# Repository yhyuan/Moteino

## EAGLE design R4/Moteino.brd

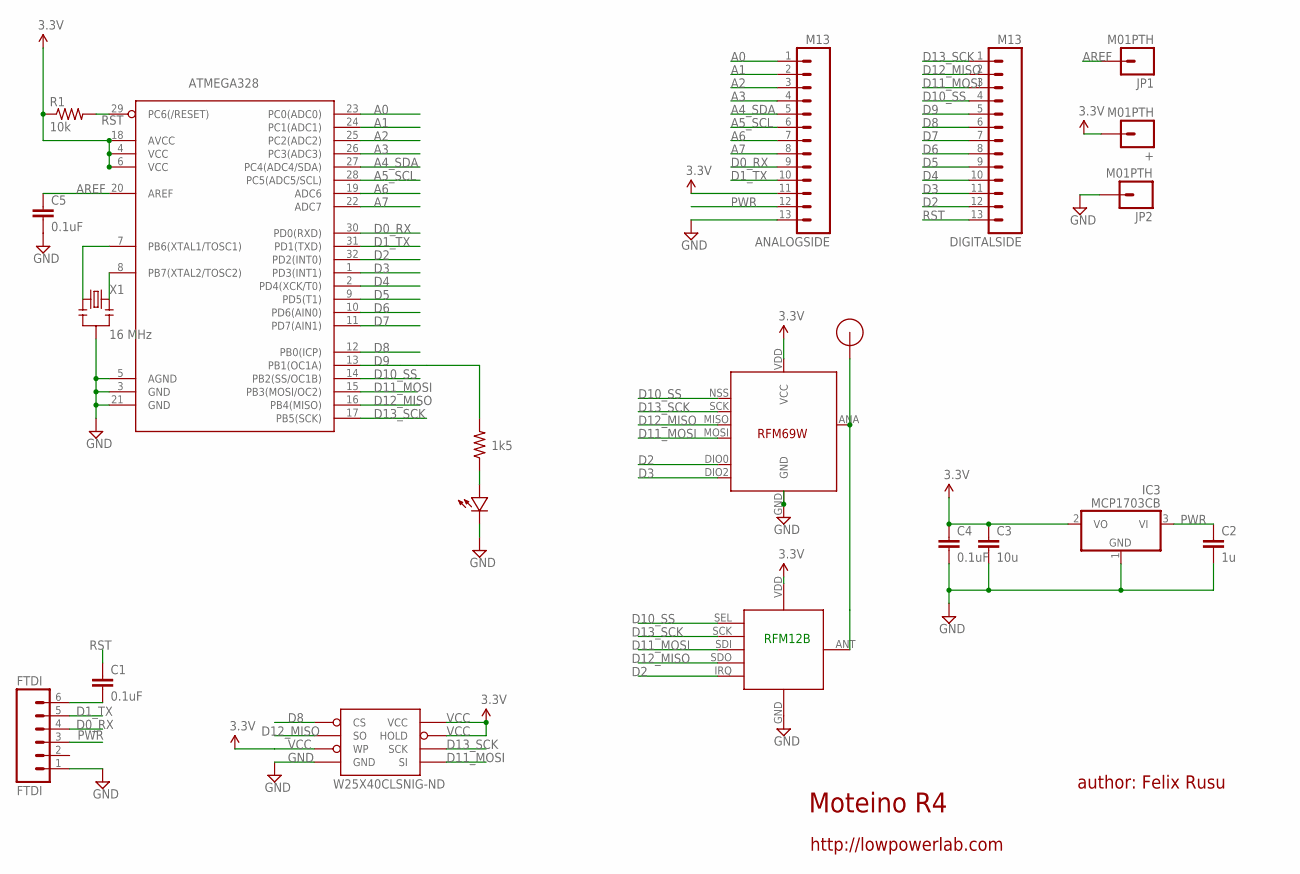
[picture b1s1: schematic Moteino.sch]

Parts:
+: M01PTH; 1X01
ANALOGSIDE: M13; 1X13
ATMEGA328: ATMega-328; TQFP32-08
C1, C4, C5: 0.1uF; 0603-CAP
C2: 1u; 0603-CAP
C3: 10u; 0805-CAP
DIGITALSIDE: M13; 1X13
FTDI: FTDI; 1X06
IC3: MCP1703CB; SOT23
JP1, JP2: M01PTH; 1X01
R1: 10k; 0603-RES
R2: 1k5; 0603-RES
RFM12B: RFM12B_MINPADS; RFM12B-MINPADS
U$1: RFM12B_ANTENNA; RFM12B-ANTENNA
U$2: LED0603; 0603-LED
U$5: RFM69; RFM69W-MINPADS
W25X40CLSNIG-ND: AT25F512BWIDE_5.3MM; SO08WIDE
X1: 16 MHz; RESONATOR-SMD

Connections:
A0: ANALOGSIDE.1, ATMEGA328.23 (PC0(ADC0))
A1: ANALOGSIDE.2, ATMEGA328.24 (PC1(ADC1))
A2: ANALOGSIDE.3, ATMEGA328.25 (PC2(ADC2))
A3: ANALOGSIDE.4, ATMEGA328.26 (PC3(ADC3))
A4_SDA: ANALOGSIDE.5, ATMEGA328.27 (PC4(ADC4/SDA))
A5_SCL: ANALOGSIDE.6, ATMEGA328.28 (PC5(ADC5/SCL))
A6: ANALOGSIDE.7, ATMEGA328.19 (ADC6)
A7: ANALOGSIDE.8, ATMEGA328.22 (ADC7)
AREF: ATMEGA328.20 (AREF), C5.1, JP1.1
D0_RX: ANALOGSIDE.9, ATMEGA328.30 (PD0(RXD)), FTDI.4
D1_TX: ANALOGSIDE.10, ATMEGA328.31 (PD1(TXD)), FTDI.5
D2: ATMEGA328.32 (PD2(INT0)), DIGITALSIDE.12, RFM12B.IRQ, U$5.DIO0
D3: ATMEGA328.1 (PD3(INT1)), DIGITALSIDE.11, U$5.DIO2
D4: ATMEGA328.2 (PD4(XCK/T0)), DIGITALSIDE.10
D5: ATMEGA328.9 (PD5(T1)), DIGITALSIDE.9
D6: ATMEGA328.10 (PD6(AIN0)), DIGITALSIDE.8
D7: ATMEGA328.11 (PD7(AIN1)), DIGITALSIDE.7
D8: ATMEGA328.12 (PB0(ICP)), DIGITALSIDE.6, W25X40CLSNIG-ND.1 (CS)
D9: ATMEGA328.13 (PB1(OC1A)), DIGITALSIDE.5, R2.2
D10_SS: ATMEGA328.14 (PB2(SS/OC1B)), DIGITALSIDE.4, RFM12B.SEL, U$5.NSS (SEL)
D11_MOSI: ATMEGA328.15 (PB3(MOSI/OC2)), DIGITALSIDE.3, RFM12B.SDI (SDI/MOSI), U$5.MOSI, W25X40CLSNIG-ND.5 (SI)
D12_MISO: ATMEGA328.16 (PB4(MISO)), DIGITALSIDE.2, RFM12B.SDO (SDO/MISO), U$5.MISO, W25X40CLSNIG-ND.2 (SO)
D13_SCK: ATMEGA328.17 (PB5(SCK)), DIGITALSIDE.1, RFM12B.SCK, U$5.SCK, W25X40CLSNIG-ND.6 (SCK)
GND: ANALOGSIDE.13, ATMEGA328.3 (GND), ATMEGA328.5 (AGND), ATMEGA328.21 (GND), C2.2, C3.2, C4.2, C5.2, FTDI.1, IC3.1 (GND), JP2.1, RFM12B.GND, U$2.MINUS, U$5.GND, W25X40CLSNIG-ND.4 (GND), X1.2
unnamed: ATMEGA328.7 (PB6(XTAL1/TOSC1)), X1.1
unnamed: R2.1, U$2.PLUS
unnamed: RFM12B.ANT, U$1.P$1, U$5.ANA (ANT)
unnamed: C1.2, FTDI.6
unnamed: ATMEGA328.8 (PB7(XTAL2/TOSC2)), X1.3
PWR: ANALOGSIDE.12, C2.1, FTDI.3, IC3.3 (VI)
RST: ATMEGA328.29 (PC6(/RESET)), C1.1, DIGITALSIDE.13, R1.2
VCC: +.1, ANALOGSIDE.11, ATMEGA328.4 (VCC), ATMEGA328.6 (VCC), ATMEGA328.18 (AVCC), C3.1, C4.1, IC3.2 (VO), R1.1, RFM12B.VDD, U$5.VDD (VCC), W25X40CLSNIG-ND.3 (WP), W25X40CLSNIG-ND.7 (HOLD), W25X40CLSNIG-ND.8 (VCC)

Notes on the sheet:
Moteino R4
author: Felix Rusu
http://lowpowerlab.com
RFM12B

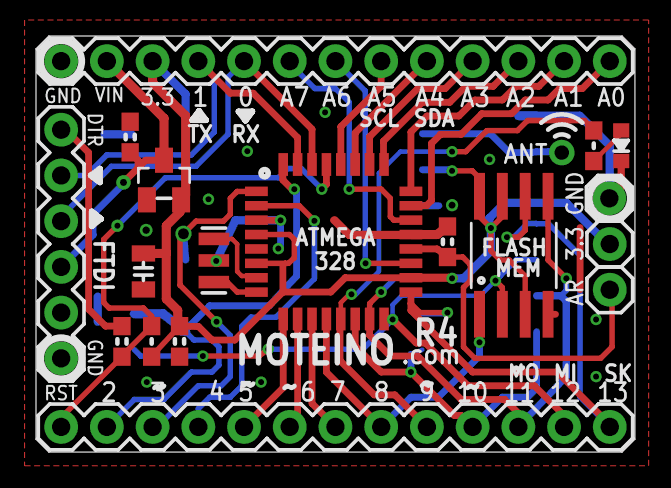
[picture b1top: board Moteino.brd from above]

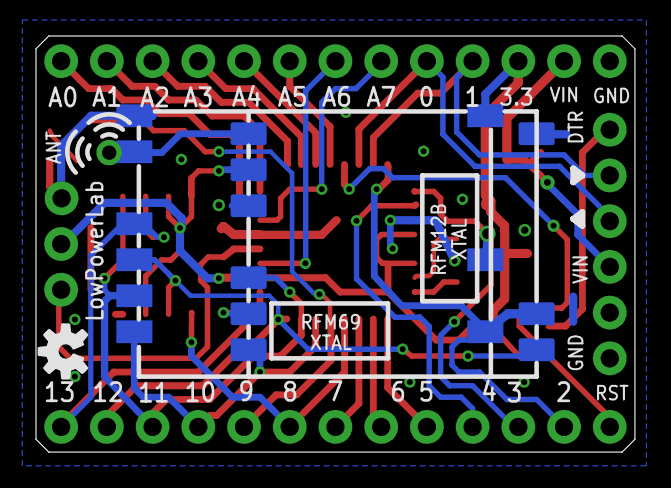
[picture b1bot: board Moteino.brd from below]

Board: 2 copper layers, 33.3 x 23.1 mm, 22 parts (3 on the bottom side), 32 nets.

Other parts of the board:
U$3: OSHW-LOGO-S

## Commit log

2015-11-10 Connect pin 3 with DIO2 https://github.com/kobuki/RFM69OOK
2015-11-13 add capacitor values

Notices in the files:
parts and their libraries:
SparkFun-Connectors: Licensing: CC v3.0 Share-Alike You are welcome to use this library for commercial purposes.
